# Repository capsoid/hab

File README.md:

# HAB - High Altitude Ballon Project

The repository contains documentation on building and launching high altitude balloon.

## Content

- **general-ideas.md** - the file lists general ideas and directions on the project;
- **flight-model** - equations and calculations on balloon motion.

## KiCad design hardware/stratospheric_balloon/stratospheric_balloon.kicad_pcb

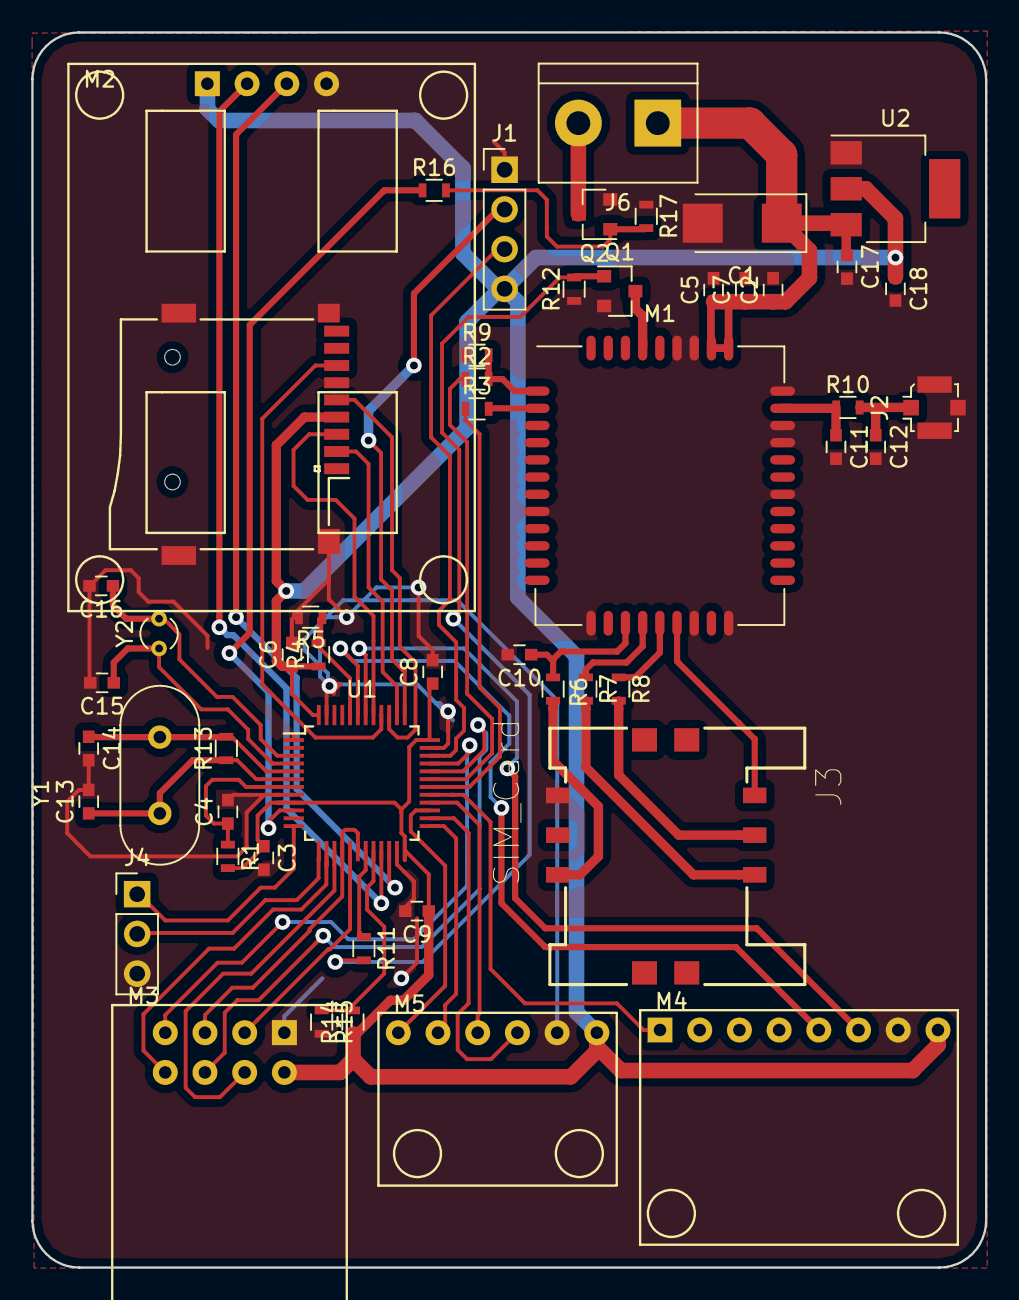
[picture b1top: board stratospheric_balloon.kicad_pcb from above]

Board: 2 copper layers, 61.0 x 79.0 mm, 52 parts (0 on the bottom side), 52 nets.

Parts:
C1: 100u; CP_Tantalum_Case-C_EIA-6032-28_Reflow
C2: 4.7u; C_0603
C3, C6, C8, C9: C_0603
C4, C10, C11, C12, C13, C14, C15, C16, C17, C18: 22p; C_0603
C5: 33p; C_0603
C7: 10p; C_0603
J1: Conn_01x04; PinHeader_1x04_P2.54mm_Vertical
J2: UFL; U.FL_Molex_MCRF_73412-0110_Vertical
J3: SIM_Card; SIM_1
J4: Conn_01x03; PinHeader_1x03_P2.54mm_Vertical
J6: Conn_01x02; TerminalBlock_bornier-2_P5.08mm
M1: SIM800C; SIMCom_SIM800C
M2: GY-GPS6MV2; GY-GPS6MV2_MODULE
M3: CC1101_MODULE_MIDDLE
M4: MPU6050_MODULE
M5: BME280_MODULE
Q1: Q_NPN_BEC; SOT-23
Q2: Q_NMOS_GSD; SOT-23
R1, R2, R3, R4, R5, R6, R7, R8, R9, R10, R11, R12, R13, R14, R15, R16, R17: R; R_0603
U1: STM32F103C8Tx; LQFP-48_7x7mm_Pitch0.5mm
U2: LM1117-3.3; SOT-223
XS1: uSD_SMD; Conn_uSDcard
Y1: Crystal; Crystal_HC49-4H_Vertical
Y2: Crystal; Crystal_Round_d2.0mm_Vertical

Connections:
+3V3: C3.1, C6.1, C8.1, C9.1, C18.1, J1.4, M2.1, M3.2, M4.8, M5.6, R1.2, R4.1, R14.1, U1.9, U1.24, U1.36, U1.48, U2.2, XS1.4
/BME_MISO2: M5.1, U1.27
/BME_MOSI2: M5.3, U1.28
/BME_NSS2: M5.2, U1.25
/BME_SCK2: M5.4, U1.26
/BURN_EN: R16.1, U1.10
/CC_CHIP_RDYn: M3.5, U1.16, U1.18
/CC_GDO0: M3.7, U1.33
/CC_GDO2: M3.6, U1.32
/CC_MOSI1: M3.3, U1.17
/CC_NSS1: M3.8, U1.14
/CC_SCK1: M3.4, U1.15
/CON_RX: J4.2, U1.13
/CON_TX: J4.1, U1.12
/GPS_RX: M2.2, U1.21
/GPS_TX: M2.3, U1.22
/GSM_PWRKEY: M1.39, Q1.3
/GSM_RX: R3.1, U1.30
/GSM_SIM_CLK: J3.3, R7.2
/GSM_SIM_DATA: J3.7, R6.2
/GSM_SIM_RST: J3.2, R8.2
/GSM_SIM_VDD: J3.1, M1.18
/GSM_TX: R2.1, U1.31
/MPU_INT: M4.1, U1.29
/MPU_SCL1: M4.6, U1.42
/MPU_SDA1: M4.5, U1.43
/PWRKEY: R11.1, U1.19
/SD_MISO: U1.40, XS1.7
/SD_MOSI: U1.41, XS1.3
/SD_NSS: U1.38, XS1.2
/SD_SCK: U1.39, XS1.5
/SWD_CLK: J1.2, U1.37
/SWD_IO: J1.3, U1.34
GND: C1.2, C2.2, C3.2, C4.2, C5.2, C6.2, C7.2, C8.2, C9.2, C10.2, C11.2, C12.2, C13.2, C14.2, C15.2, C16.2, C17.2, C18.2, J1.1, J2.2, J3.5, J4.3, M1.8, M1.13, M1.19, M1.21, M1.27, M1.30, M1.31, M1.33, M1.36, M1.37, M2.4, M3.1, M4.7, M5.5, Q1.2, Q2.2, R5.2, R9.1, R12.1, R15.2, R17.1, U1.1, U1.8, U1.23, U1.35, U1.47, U2.1, XS1.6
unnamed: C4.1, R1.1, U1.7
unnamed: C10.1, M1.15, R6.1
unnamed: C11.1, M1.32, R10.1
unnamed: C12.1, J2.1, R10.2
unnamed: C13.1, R13.1, U1.6, Y1.1
unnamed: C14.1, R13.2, U1.5, Y1.2
unnamed: C15.1, U1.4, Y2.1
unnamed: C16.1, U1.3, Y2.2
unnamed: J6.2, Q2.3
unnamed: M1.1, R2.2, R9.2
unnamed: M1.2, R3.2
unnamed: M1.16, R7.1
unnamed: M1.17, R8.1
unnamed: Q1.1, R11.2, R12.2
unnamed: Q2.1, R16.2, R17.2
unnamed: R4.2, R5.1, U1.44
unnamed: R14.2, R15.1, U1.20
VBAT: C1.1, C2.1, C5.1, C7.1, C17.1, J6.1, M1.34, M1.35, U2.3

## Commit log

2018-11-19 Add file for general ideas
2018-11-20 Update general-ideas.md
    Added HAB projects links
2018-11-20 Update general-ideas.md
    .md formatting applied :)
2018-11-21 Add balloon and helium options
2018-11-22 Add lift calculations
2018-11-22 Add note on pressure-size experiment
2018-11-25 Add payload cooling experiment note
2018-11-27 Added smoke test results
2018-12-03 Add zephyr project for stm32 blue pill
2018-12-03 Add example code for working with BME280
2018-12-03 Improve debugging expirience
    - compile with optimization turned off
    - redirect sdtout to console output
    - add .phony target for generating ctags index
2018-12-03 Enable zephyr shell
2018-12-04 Schematic added
2018-12-04 Add Friis formula xls
2018-12-04 Fix README format
2018-12-04 A bit more of SPI
2018-12-06 Enable spi1
2018-12-06 Add cc1101 library sources from TI
2018-12-09 Add cc1101 code skeleton, not tested, not working
2018-12-09 Added first data on size-pressure experiment
2018-12-09 Add size-pressure experiment schema; Round volume data on the graph
2018-12-09 Scale down size-pressure experiment schema
2018-12-10 Schematic diagram was corrected
2018-12-10 Add shell skeleton
2018-12-11 Account for CHIP_RDYn pin
2018-12-12 Reconfigure to see threads info from shell
2018-12-13 Adjust cc1101 pin connections according to schematics
2018-12-13 Add mpu6050 code without cfg
2018-12-14 Fix spi data format
2018-12-16 Add results of size-pressure experiment for 36"
2018-12-16 Add flight predictor link
2018-12-18 Enable MPU6050 reading
2018-12-19 Add some checks
2018-12-19 Add mpu6050 manual reset
2018-12-20 Fix mpu6050 values displaying
2018-12-20 Add cc1101 driver implementation from PR
2018-12-20 Crunch in cc1101 driver
2018-12-21 Add DEVICE_INIT and gpios conf
2018-12-21 Fix cc1101 initalization
    Still crashes when RX thread is spawned ...
2018-12-22 Add RF beacon
2018-12-22 Setup channel and tx power on startup
2018-12-27 Fix gpio configuration
2018-12-28 Fix gpio interrupts conf
2018-12-28 Something finally started to work over rf
2019-03-28 Add mcu and modem schematic components
2019-04-04 Add some components for GSM and MCU
2019-04-07 Put all components on A4. Do connectians.
2019-04-07 Add SIM and microsd slots
2019-04-10 Add footprints for GPS, GSM, BME, MPU
2019-04-20 Add some footprints
2019-04-22 Assign some footprints to sch elements
2019-04-26 Fix mistakes with footprints. Do layout
2019-05-01 Add some changes in layout
2019-07-12 Change vias. Add power planes
2019-07-24 Add vias
2019-07-24 Add origin. Add sizes.
2019-08-04 Add some values
2019-08-04 Restore ability to build
2019-08-13 Add layout
2019-12-26 WIP: add new prj.config
2020-01-03 Add deployment script
2020-01-09 Add zephyr modules
2020-01-09 Update prj.conf to restore build
2020-01-10 Update gitignore
2020-01-14 Add openocd configuration
2020-01-26 Expand .gitignore to ignore west output
2020-02-09 Change config to use UART_2 as console output, remap cc1101 output to resole conflict with UART_2
2020-02-10 Create stub for bme280 device in dts
2020-02-10 Change slave select to 2
2020-02-11 Enable MPU6050 in Kconfig
2020-02-14 Change MPU interruption pin and i2c clock speed
2020-02-27 Add clang format and gps command stub
2020-02-28 Create basic device for GPS
2020-02-28 Add header file
2020-03-04 Add ring buffer for reading gps via interrupts
2020-07-09 Replace ringbuf with simple array
